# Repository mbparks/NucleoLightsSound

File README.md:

# NucleoLightsSound

This project is meant to help teach basic electronics including voltage dividers, potentiometers, op-amps, feedback, capacitors, RC filters, microcontrollers, ADC, and C/C++ programming.

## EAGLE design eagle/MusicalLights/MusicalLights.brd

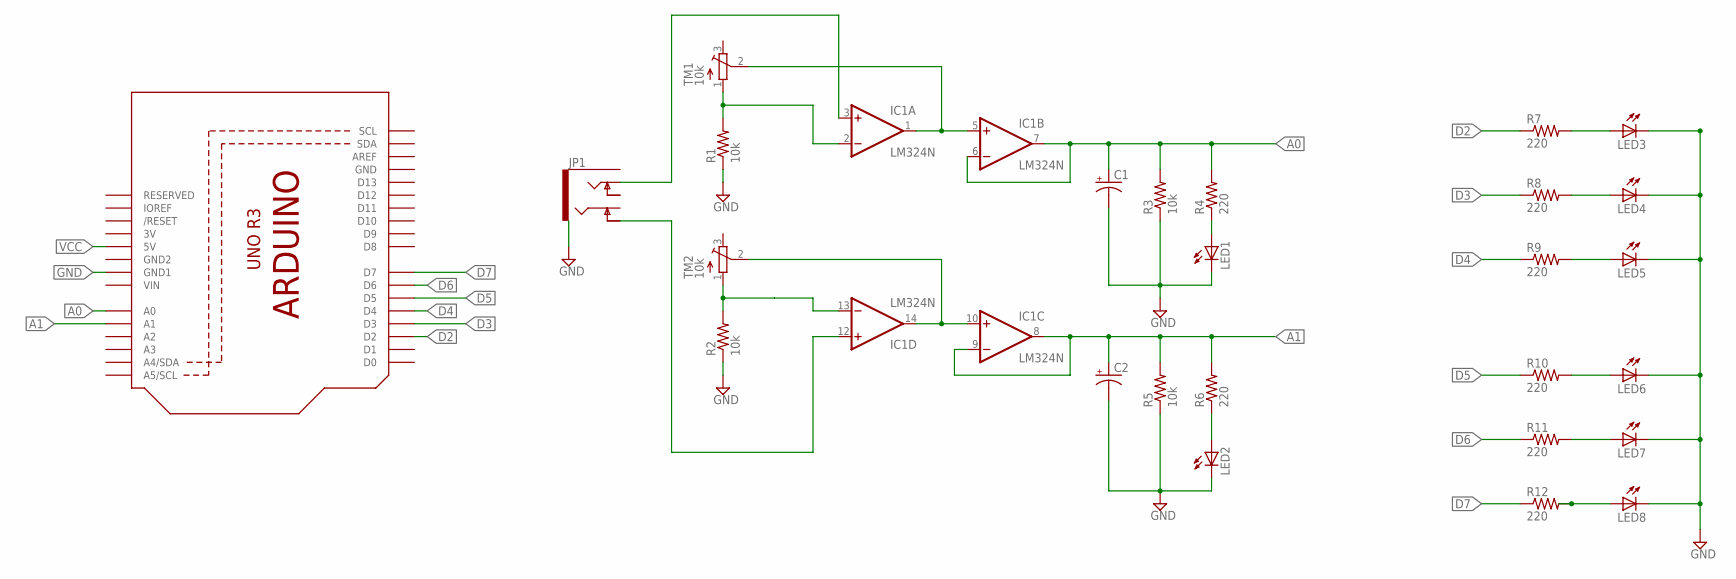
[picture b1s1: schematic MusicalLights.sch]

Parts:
C1, C2: CAP_POLPTH2; CPOL-RADIAL-10UF-25V
IC1: LM324N; DIL14
JP1: AUDIO-JACK5-.25-VERT-TRS; AUDIO-JACK-.25-INCH-VERT-PTH
LED1, LED2, LED3, LED4, LED5, LED6, LED7, LED8: LED5MM
R1, R2, R3, R5: 10k; 0207/10
R4, R6, R7, R8, R9, R10, R11, R12: 220; 0207/10
TM1, TM2: 10k; TRIM-3386
U1: ARDUINOR3-DIMENSION; ARDUINOR3

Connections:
3V: U1.3V
A0: C1.1 (+), IC1.6 (-IN), IC1.7 (OUT), R3.2, R4.2, U1.A0
A1: C2.1 (+), IC1.8 (OUT), IC1.9 (-IN), R5.2, R6.2, U1.A1
D2: R7.1, U1.D2
D3: R8.1, U1.D3
D4: R9.1, U1.D4
D5: R10.1, U1.D5
D6: R11.1, U1.D6
D7: R12.1, U1.D7
GND: C1.2 (-), C2.2 (-), LED1.K (C), LED2.K (C), LED3.K (C), LED4.K (C), LED5.K (C), LED6.K (C), LED7.K (C), LED8.K (C), R1.1, R2.1, R3.1, R5.1, U1.GND, U1.GND1
GND2: U1.GND2
unnamed: IC1.2 (-IN), R1.2, TM1.1 (A)
unnamed: IC1.13 (-IN), R2.2, TM2.1 (A)
unnamed: IC1.3 (+IN), JP1.TIP
unnamed: IC1.12 (+IN), JP1.RING-NORM
unnamed: IC1.1 (OUT), IC1.5 (+IN), TM1.2 (S)
unnamed: IC1.10 (+IN), IC1.14 (OUT), TM2.2 (S)
unnamed: LED3.A, R7.2
unnamed: LED2.A, R6.1
unnamed: LED1.A, R4.1
unnamed: LED4.A, R8.2
unnamed: LED5.A, R9.2
unnamed: LED6.A, R10.2
unnamed: LED7.A, R11.2
unnamed: LED8.A, R12.2
V+: IC1.4 (V+)
V-: IC1.11 (V-)
VCC: U1.5V
VIN: U1.VIN

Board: 2 copper layers, 27 parts (0 on the bottom side), 23 nets, no tracks yet.

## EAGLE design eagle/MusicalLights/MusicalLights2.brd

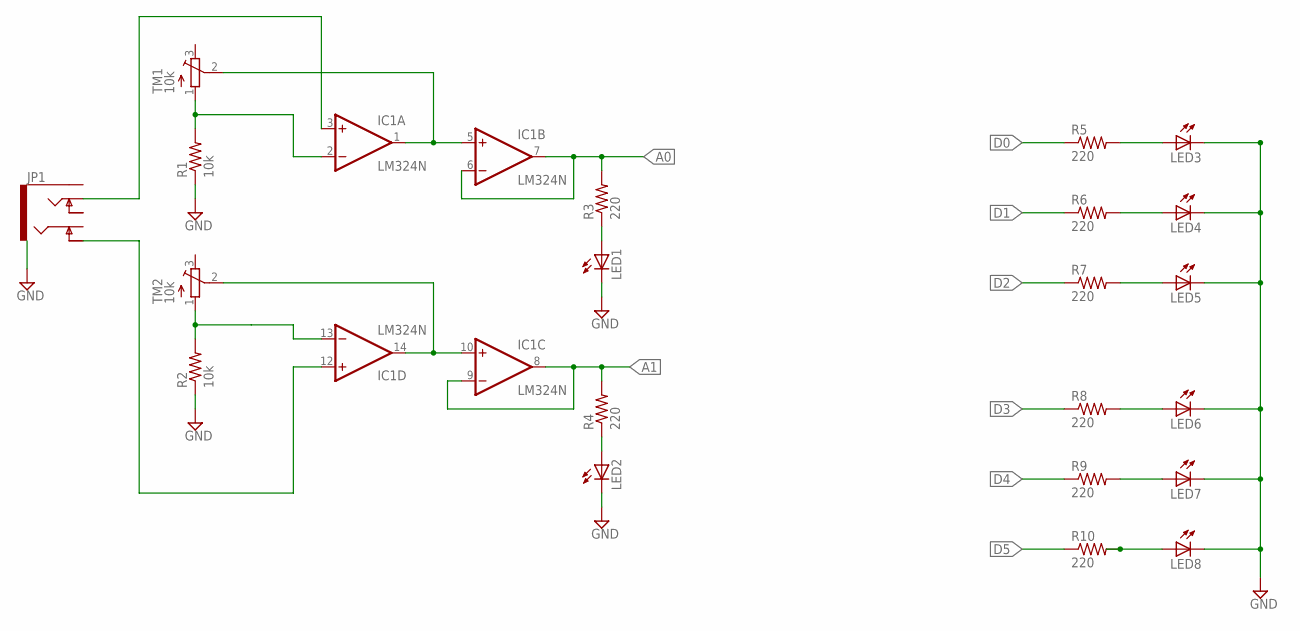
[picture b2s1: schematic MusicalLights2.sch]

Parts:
IC1: LM324N; DIL14
JP1: AUDIO-JACK5-.25-VERT-TRS; AUDIO-JACK-.25-INCH-VERT-PTH
LED1, LED2, LED3, LED4, LED5, LED6, LED7, LED8: LED5MM
R1, R2: 10k; 0207/10
R3, R4, R5, R6, R7, R8, R9, R10: 220; 0207/10
TM1, TM2: 10k; TRIM-3386

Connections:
A0: IC1.6 (-IN), IC1.7 (OUT), R3.2
A1: IC1.8 (OUT), IC1.9 (-IN), R4.2
D0: R5.1
D1: R6.1
D2: R7.1
D3: R8.1
D4: R9.1
D5: R10.1
GND: LED1.K (C), LED2.K (C), LED3.K (C), LED4.K (C), LED5.K (C), LED6.K (C), LED7.K (C), LED8.K (C), R1.1, R2.1
unnamed: IC1.2 (-IN), R1.2, TM1.1 (A)
unnamed: IC1.13 (-IN), R2.2, TM2.1 (A)
unnamed: IC1.3 (+IN), JP1.TIP
unnamed: IC1.12 (+IN), JP1.RING-NORM
unnamed: IC1.1 (OUT), IC1.5 (+IN), TM1.2 (S)
unnamed: IC1.10 (+IN), IC1.14 (OUT), TM2.2 (S)
unnamed: LED3.A, R5.2
unnamed: LED2.A, R4.1
unnamed: LED1.A, R3.1
unnamed: LED4.A, R6.2
unnamed: LED5.A, R7.2
unnamed: LED6.A, R8.2
unnamed: LED7.A, R9.2
unnamed: LED8.A, R10.2
V+: IC1.4 (V+)
V-: IC1.11 (V-)

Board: 2 copper layers, 22 parts (0 on the bottom side), 17 nets, no tracks yet.

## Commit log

2015-05-29 init release
2015-06-14 update support doc
    include new images to help teach the underlying electronics, fixed
    resistor values in schematic

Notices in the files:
parts and their libraries:
SparkFun-Connectors: Licensing: Creative Commons ShareAlike 4.0 International - https://creativecommons.org/licenses/by-sa/4.0
